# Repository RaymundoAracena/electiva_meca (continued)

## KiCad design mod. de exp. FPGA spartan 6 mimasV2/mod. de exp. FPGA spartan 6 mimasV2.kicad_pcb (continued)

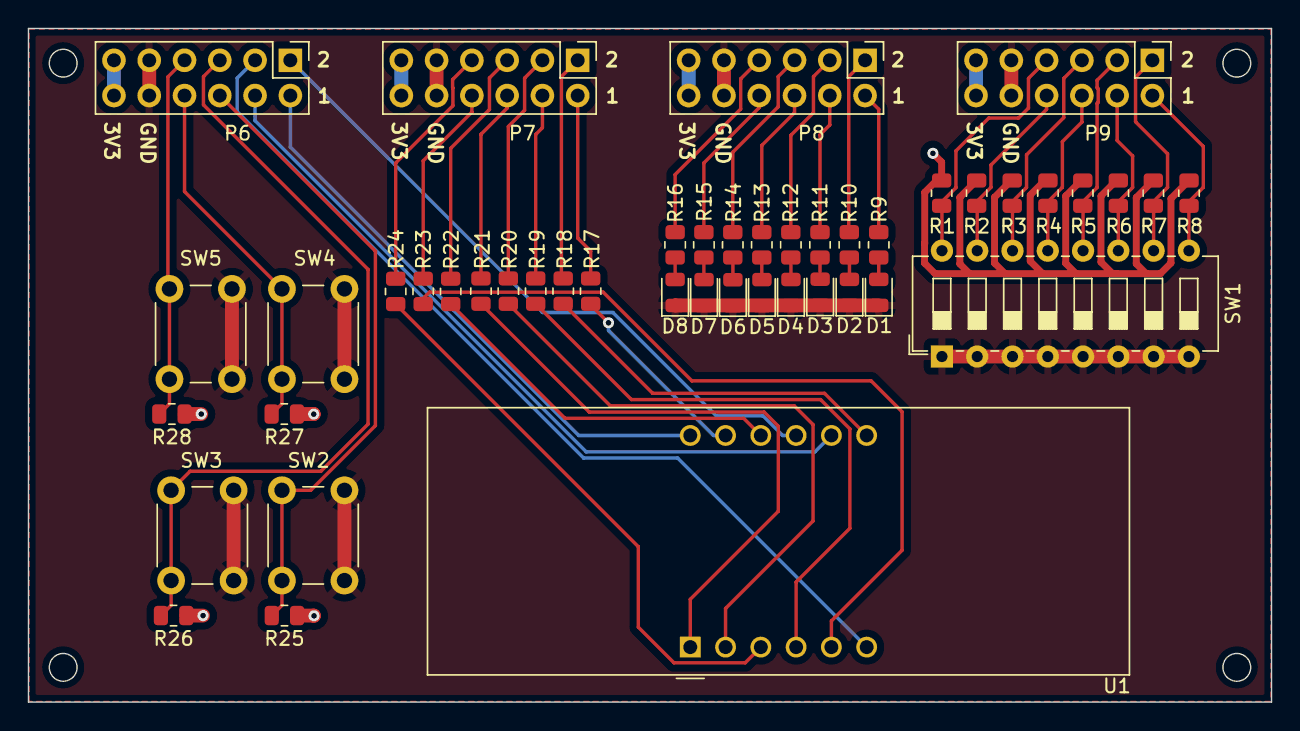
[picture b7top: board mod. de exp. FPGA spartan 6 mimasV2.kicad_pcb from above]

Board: 2 copper layers, 89.5 x 48.5 mm, 46 parts (0 on the bottom side), 50 nets.

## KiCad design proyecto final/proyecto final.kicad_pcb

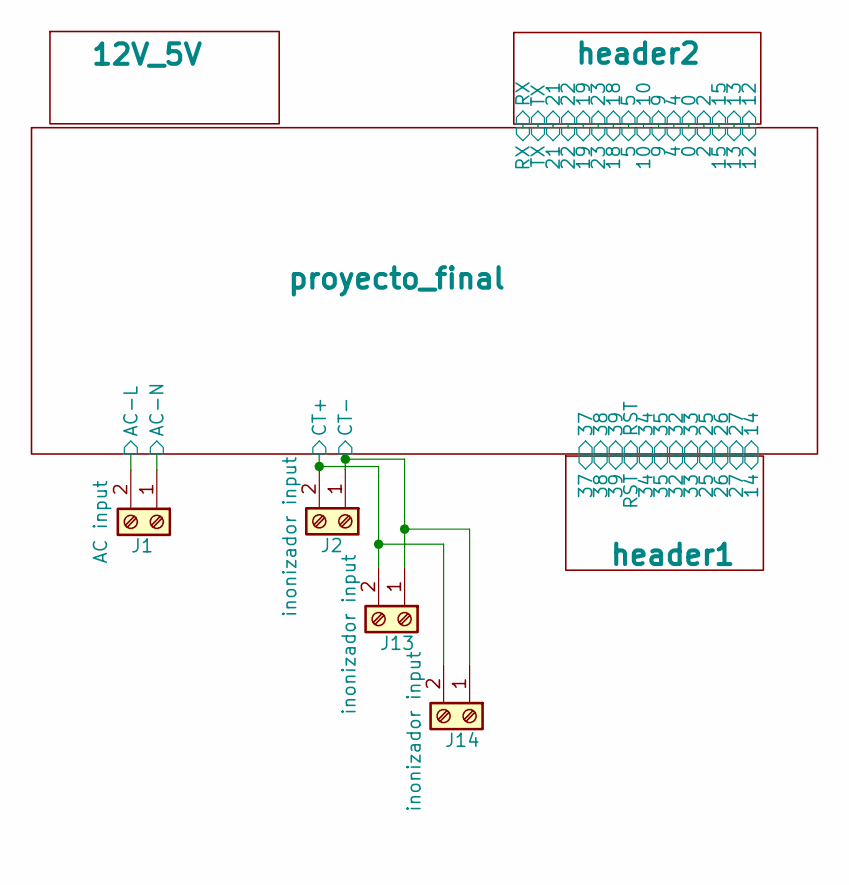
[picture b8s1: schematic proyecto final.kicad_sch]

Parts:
J1: AC input; TerminalBlock_bornier-2_P5.08mm
J2: inonizador input; TerminalBlock_bornier-2_P5.08mm
J13: inonizador input; PinSocket_1x02_P2.54mm_Vertical
J14: inonizador input; JST_EH_B2B-EH-A_1x02_P2.50mm_Vertical

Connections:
/proyecto_final/AC-L: J1.2; also elsewhere on the board
/proyecto_final/AC-N: J1.1; also elsewhere on the board
/proyecto_final/CT+: J2.2, J13.2, J14.2; also elsewhere on the board
GND: J2.1, J13.1, J14.1; also elsewhere on the board

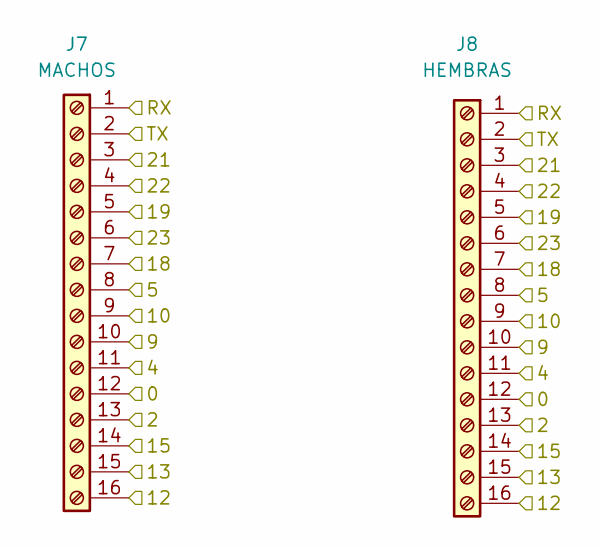
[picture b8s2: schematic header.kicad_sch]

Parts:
J7: MACHOS; PinHeader_1x16_P2.54mm_Vertical
J8: HEMBRAS; PinSocket_1x16_P2.54mm_Vertical

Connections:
/header2/0: J7.12, J8.12; also elsewhere on the board
/header2/2: J7.13, J8.13; also elsewhere on the board
/header2/4: J7.11, J8.11; also elsewhere on the board
/header2/5: J7.8, J8.8; also elsewhere on the board
/header2/9: J7.10, J8.10; also elsewhere on the board
/header2/10: J7.9, J8.9; also elsewhere on the board
/header2/12: J7.16, J8.16; also elsewhere on the board
/header2/13: J7.15, J8.15; also elsewhere on the board
/header2/15: J7.14, J8.14; also elsewhere on the board
/header2/18: J7.7, J8.7; also elsewhere on the board
/header2/19: J7.5, J8.5; also elsewhere on the board
/header2/21: J7.3, J8.3; also elsewhere on the board
/header2/22: J7.4, J8.4; also elsewhere on the board
/header2/23: J7.6, J8.6; also elsewhere on the board
/header2/RX: J7.1, J8.1; also elsewhere on the board
/header2/TX: J7.2, J8.2; also elsewhere on the board

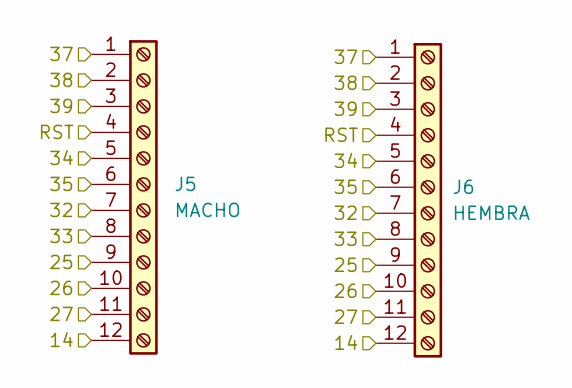
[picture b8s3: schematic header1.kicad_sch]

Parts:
J5: MACHO; PinHeader_1x12_P2.54mm_Vertical
J6: HEMBRA; PinSocket_1x12_P2.54mm_Vertical

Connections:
/header1/14: J5.12, J6.12; also elsewhere on the board
/header1/25: J5.9, J6.9; also elsewhere on the board
/header1/26: J5.10, J6.10; also elsewhere on the board
/header1/27: J5.11, J6.11; also elsewhere on the board
/header1/32: J5.7, J6.7; also elsewhere on the board
/header1/33: J5.8, J6.8; also elsewhere on the board
/header1/34: J5.5, J6.5; also elsewhere on the board
/header1/35: J5.6, J6.6; also elsewhere on the board
/header1/37: J5.1, J6.1; also elsewhere on the board
/header1/38: J5.2, J6.2; also elsewhere on the board
/header1/39: J5.3, J6.3; also elsewhere on the board
/header1/RST: J5.4, J6.4; also elsewhere on the board

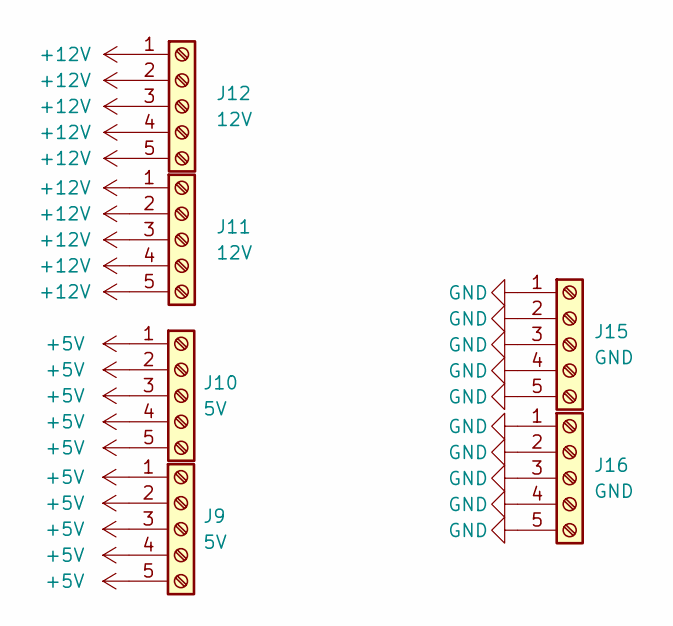
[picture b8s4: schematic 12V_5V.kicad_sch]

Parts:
J9: 5V; PinSocket_1x05_P2.54mm_Vertical
J10: 5V; PinHeader_1x05_P2.54mm_Vertical
J11: 12V; PinHeader_1x05_P2.54mm_Vertical
J12: 12V; PinSocket_1x05_P2.54mm_Vertical
J15: GND; PinSocket_1x05_P2.54mm_Vertical
J16: GND; PinHeader_1x05_P2.54mm_Vertical

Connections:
+5V: J9.1, J9.2, J9.3, J9.4, J9.5, J10.1, J10.2, J10.3, J10.4, J10.5; also elsewhere on the board
+12V: J11.1, J11.2, J11.3, J11.4, J11.5, J12.1, J12.2, J12.3, J12.4, J12.5; also elsewhere on the board
GND: J15.1, J15.2, J15.3, J15.4, J15.5, J16.1, J16.2, J16.3, J16.4, J16.5; also elsewhere on the board

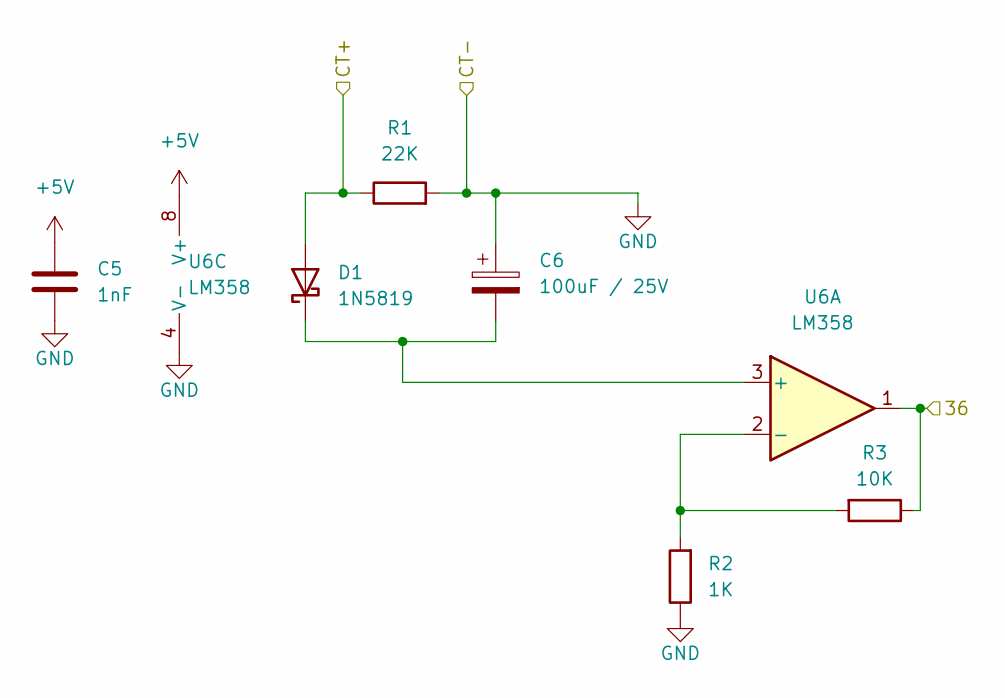
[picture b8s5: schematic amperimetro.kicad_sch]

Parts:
C5: 1nF; C_0805_2012Metric
C6: 100uF / 25V; CP_Radial_D6.3mm_P2.50mm
D1: 1N5819; D_DO-41_SOD81_P10.16mm_Horizontal
R1: 22K; R_0805_2012Metric
R2: 1K; R_0805_2012Metric
R3: 10K; R_0805_2012Metric
U6: LM358; SOP-8_3.9x4.9mm_P1.27mm

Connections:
+5V: C5.1, U6.8 (V+); also elsewhere on the board
/proyecto_final/CT+: D1.2 (A), R1.1; also elsewhere on the board
/proyecto_final/amperimetro/36: R3.1, U6.1; also elsewhere on the board
GND: C5.2, C6.1, R1.2, R2.1, U6.4 (V-); also elsewhere on the board
unnamed: C6.2, D1.1 (K), U6.3 (+)
unnamed: R2.2, R3.2, U6.2 (-)

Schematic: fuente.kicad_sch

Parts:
C1: 0.33uF; C_0805_2012Metric
C2: 0.22uF; C_0805_2012Metric
C3: 2.2uF (ceramico); C_0805_2012Metric
C4: 0.1uF; C_0805_2012Metric
C7, C8: 100uF / 25V; CP_Radial_D6.3mm_P2.50mm
D2, D3, D4: LED; LED_0805_2012Metric
F1: Fuse; Fuseholder_Clip-5x20mm_Keystone_3517_Inline_P23.11x6.76mm_D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
PS1: HLK-PM12; Converter_ACDC_HiLink_HLK-PMxx
R4, R5, R6: R; R_0805_2012Metric
RV1: V10E275P; VAR_B72210S1140K501
U1, U4, U5: fuse_CC12H1.5A-TR; CC12H1.5A-TR
U2: 3v3 NJM2885DL1-33; TO-252-2
U3: LM7805_TO220; TO-220-3_Vertical

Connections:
+3V3: D4.2 (A), U4.2; also elsewhere on the board
+5V: D3.2 (A), U5.2; also elsewhere on the board
+12V: C1.1, C2.1, C7.1, C8.1, D2.2 (A), U1.2, U2.1 (Vin), U3.1 (VI); also elsewhere on the board
/proyecto_final/AC-L: F1.2; also elsewhere on the board
/proyecto_final/AC-N: PS1.2 (AC/N), RV1.2; also elsewhere on the board
GND: C1.2, C2.2, C3.2, C4.2, C7.2, C8.2, PS1.3 (-Vout), R4.2, R5.2, R6.2, U2.2 (GND), U3.2 (GND); also elsewhere on the board
unnamed: C3.1, U2.3 (Vout), U4.1
unnamed: C4.1, U3.3 (VO), U5.1
unnamed: D2.1 (K), R4.1
unnamed: D3.1 (K), R5.1
unnamed: D4.1 (K), R6.1
unnamed: F1.1, PS1.1 (AC/L), RV1.1
unnamed: PS1.4 (+Vout), U1.1

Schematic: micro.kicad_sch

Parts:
J3: IO_IZQUIERDA; PinSocket_1x17_P2.54mm_Vertical
J4: IO_DERECHA; PinSocket_1x17_P2.54mm_Vertical
SW1: 5V; PinHeader_1x02_P2.54mm_Vertical
SW2: 3V3; PinHeader_1x02_P2.54mm_Vertical

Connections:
+3V3: SW2.1; also elsewhere on the board
+5V: SW1.1; also elsewhere on the board
+5VA: J3.16, SW1.2
/header1/14: J3.15; also elsewhere on the board
/header1/25: J3.12; also elsewhere on the board
/header1/26: J3.13; also elsewhere on the board
/header1/27: J3.14; also elsewhere on the board
/header1/32: J3.10; also elsewhere on the board
/header1/33: J3.11; also elsewhere on the board
/header1/34: J3.8; also elsewhere on the board
/header1/35: J3.9; also elsewhere on the board
/header1/37: J3.4; also elsewhere on the board
/header1/38: J3.5; also elsewhere on the board
/header1/39: J3.6; also elsewhere on the board
/header1/RST: J3.7; also elsewhere on the board
/header2/0: J4.13; also elsewhere on the board
/header2/2: J4.14; also elsewhere on the board
/header2/4: J4.12; also elsewhere on the board
/header2/5: J4.9; also elsewhere on the board
/header2/9: J4.11; also elsewhere on the board
/header2/10: J4.10; also elsewhere on the board
/header2/12: J4.17; also elsewhere on the board
/header2/13: J4.16; also elsewhere on the board
/header2/15: J4.15; also elsewhere on the board
/header2/18: J4.8; also elsewhere on the board
/header2/19: J4.6; also elsewhere on the board
/header2/21: J4.4; also elsewhere on the board
/header2/22: J4.5; also elsewhere on the board
/header2/23: J4.7; also elsewhere on the board
/header2/RX: J4.2; also elsewhere on the board
/header2/TX: J4.3; also elsewhere on the board
/proyecto_final/amperimetro/36: J3.3; also elsewhere on the board
GND: J3.1, J3.17, J4.1; also elsewhere on the board
unnamed: J3.2, SW2.2

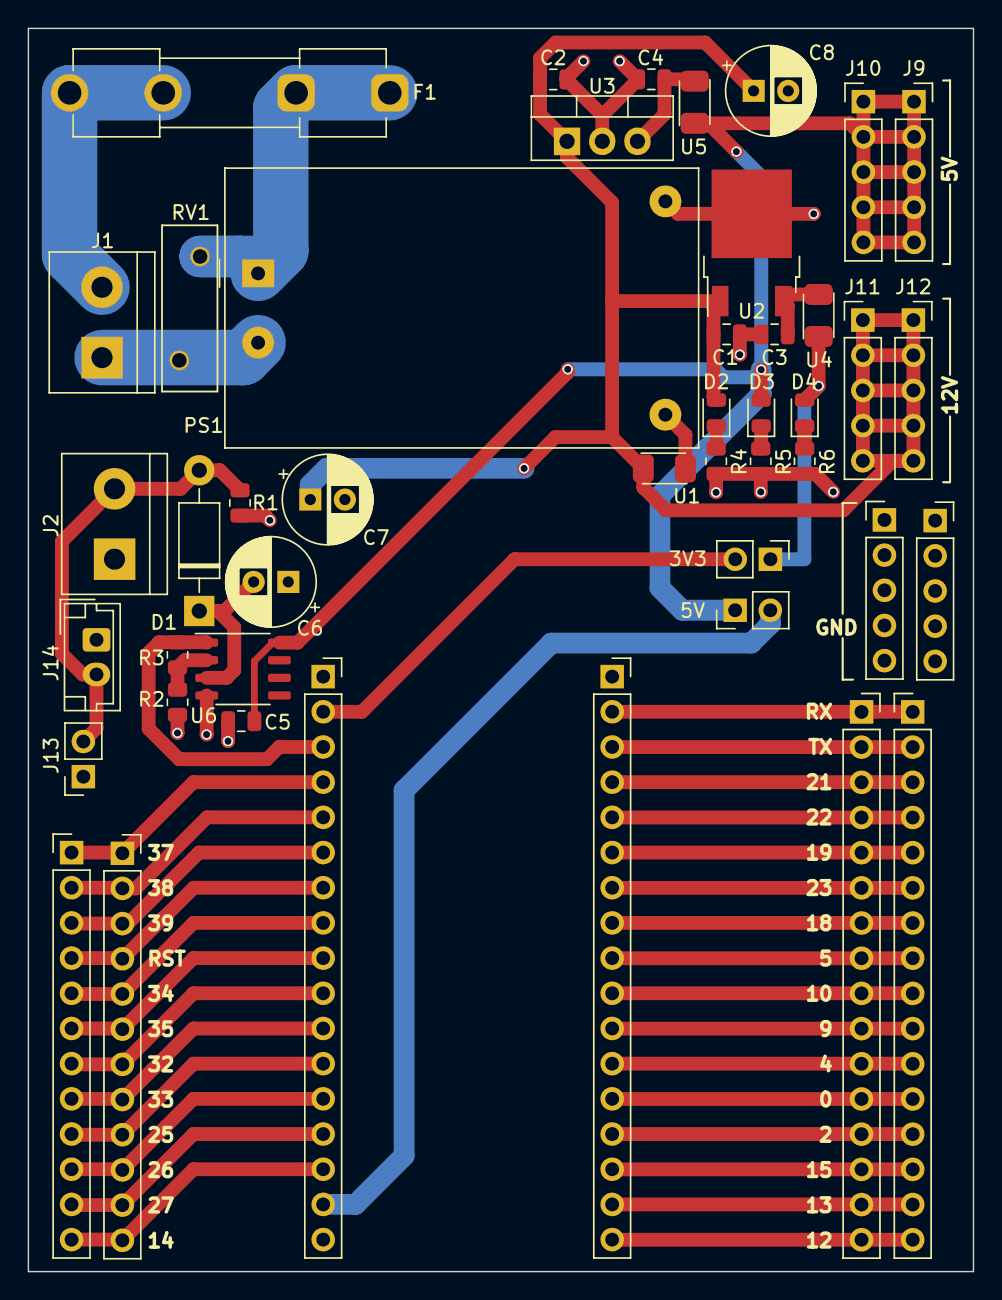
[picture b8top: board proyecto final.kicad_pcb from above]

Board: 2 copper layers, 68.2 x 89.7 mm, 45 parts (0 on the bottom side), 47 nets.

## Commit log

2023-05-20 saludo buenas como se encuentra mi estimado
2023-05-20 PDF resumen de pichardo
2023-06-02 Se añadió el diseño del pcb
2023-06-02 esquema esp32
2023-06-14 añadi el pcb de prueba de dispostivo
2023-06-20 primer modelo del modulo de expancion del fpga
2023-06-20 primer modelo del esquema de proyecto de cuatrimestre
2023-06-21 la baina
2023-06-23 modulo de prueba de ic
2023-06-23 PRIMER MODELO PROYECTO FINAL ESP32
2023-06-23 CAMBIO DE HEADER
2023-06-29 remasturizacion
2023-06-29 el SMD del FPGA modul
2023-06-29 el THT del FPGA modul
2023-07-20 esquematico de robotica
2023-07-20 PCB YA REALIZADO
2023-07-21 termincacion del pcb de robotica
2023-07-25 absolutamente todo
2023-07-28 ULTIMA ACTUALIZACION
2023-08-18 terminacion
